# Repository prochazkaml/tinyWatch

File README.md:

# tinyWatch

A simple ATtiny3224-based wristwatch with an OLED display, a couple of buttons and a CR2032 battery.

To build your very own tinyWatch, you'll need to source the components, get a PCB made (or make it yourself, if you're brave enough), get the plastic parts 3D printed (or, again, print it yourself if you've already got a printer) and find a compatible 18 mm watch band + push pin (or edit the .scad files if you've got some other one).

## Plastic parts

The plastic parts of the tinyWatch are expected to be 3D printed (tested FDM, but SLA should work as well). They consist of:

- the back piece where the battery and PCB will be fit
- the front piece which will hold the OLED panel as well as the buttons in place, it also contains a pair of holes at each end for fitting a watch band push pin
- OLED support piece which will make the panel not fall inside of the watch
- 3x button caps

You can find these in the [hw/3D](https://github.com/prochazkaml/tinyWatch/tree/master/hw/3D) directory in .stl format with the .scad source files are available as well.

These parts are held together with an **M3 nut and M3x6 screw**.

## PCB & Hardware

The circuit diagram as well as the PCB were designed in KiCad, the project files are available in the [hw/kicad](https://github.com/prochazkaml/tinyWatch/tree/master/hw/kicad) directory. Many prototype PCB manufacturers support uploading raw KiCad files directly without the need to generate Gerber files. Recommended PCB thickness is 1.6 mm.

Of course, you will then need to populate the manufactured PCB with components. The bill of materials is available [here](https://github.com/prochazkaml/tinyWatch/blob/master/hw/kicad/tinywatch.csv) in CSV format. In summary, you'll need:

|Component|Package|Qty|DigiKey Part Number|
|-|-|-|-|
|4.7 μF capacitor|0603|1|1276-1044-1-ND|
|1 μF capacitor|0603|5|1276-1946-1-ND|
|2.2 μF capacitor|0603|1|1276-1040-1-ND|
|10 μF capacitor|0603|1|1276-1119-1-ND|
|1N4148W diode|SOD-123|1|311-4.70KHRTR-ND|
|4-pin straight female header|4x2.54 pitch|1|S7037-ND|
|SSD1306 128x64 0.96" OLED panel|30 pin flat ribbon, 0.7 mm pitch|1|3190-DLC0096DNOG-W-5-ND (but you can probably get it much cheaper [elsewhere](https://www.aliexpress.com/item/1005006114087000.html))|
|910k resistor|0603|1|13-AC0603FR-07910KLTR-ND|
|4.7k resistor|0603|1|311-4.70KHRTR-ND|
|Push button|6.7x4.1 mm|3|CKN12330-1-ND|
|ATtiny3224|SOIC-14|1|150-ATTINY3224-SSURCT-ND|
|32.768 kHz oscillator|3.2x2.5 mm|1|50-ECS-327TXO-30-CT-ND|

What is not included in the BOM is a **CR2032** battery, with specially shaped nickel strips welded to its terminals.
The assembly instructions below go into more detail on how to prepare and connect the battery correctly.

A cheap and perfectly usable watch band is available for example from [here](https://www.aliexpress.com/item/1005002369169370.html), just remember to select the 18 mm option. I personally opted for the "ML-Black" variant, it works just fine; it even comes with the required push pins embedded into the straps themselves.

## Assembly instructions

The hardware assembly instructions are available in [a separate document](ASSEMBLY.md).

Please note that the document already assumes that you have already assembled the required components onto the tinyWatch mainboard (excluding the battery).

## Firmware building instructions

The tinyWatch's firmware is written in Rust, so you'll need the Rust toolchain to be installed.

Bulding the firmware is as easy as running the following command:

```bash
cargo build --release
```

**NOTE**: This firmware is currently only compatible with revision 2 hardware with the new ATtiny3224 microcontroller. The old revision 1 hardware is only supported by the [old C-based firmware](https://github.com/prochazkaml/tinyWatch/tree/2073f80b21bf5213d320747aeb9541f89d2ae41b).

If you have a [serialupdi](https://github.com/SpenceKonde/AVR-Guidance/blob/master/UPDI/jtag2updi.md) programmer attached to the PC as well as the watch and want to upload the firmware to the watch, run the following:

```bash
avrdude -p attiny3224 -c serialupdi -P /dev/ttyUSB0 -v -U flash:w:target/avr-none/release/tinywatch.elf
```

## Power consumption

The watch consumes roughly **4.4 mA** while the screen is on, and about **3.4 μA** while the screen is off.

If you look at your watch for a total of 5 minutes each day, that would result in about **447 μAh** of power consumption **per day**. With this usage, the 220 mAh battery in the watch should last **more than a year**.

These measurements were taken using Nordic's [Power Profiler Kit 2](https://www.nordicsemi.com/Products/Development-hardware/Power-Profiler-Kit-2). The [raw capture file](doc/tinywatch_power_consumption.ppk2) can be viewed in the Power Profiler applet of the free and open source [nRF Connect for Desktop](https://www.nordicsemi.com/Products/Development-tools/nRF-Connect-for-Desktop) software.

## Setup

After flashing the firmware, you will want to set up the clock.
To do that, press the **left and right button** at simultaneously.
Then, using the **left** and **right** button, you will set the value on-screen and then press the **middle** button to confirm your selection and move onto the next value or finish the clock setup if you're done.
You will be asked at the end whether the entered values are correct.

## Oscillator calibration

> [!NOTE]  
> Revision 2 hardware uses a high quality temperature-compensated crystal oscillator with at most ±5 ppm of error, resulting in less than 0.5 seconds of drift per day.
> With this hardware, this option should be left alone.

If you experience severe drifts with the watch (more than 1 second per day), it is possible to trim the oscillator to a more precise value.

To remedy this issue, press the **left and middle button** together to enter the clock calibration menu.
There, you will be presented by a 16-bit hex value (the default is 8000, corresponding to the 32.768 kHz of the main oscillator).
With the **left** and **right** button, you can move the cursor.

To edit a value of a digit, press the **middle** button (the cursor will appear above the digit so that it is apparent what the buttons currently do)
and adjust the value using the **left** and **right** button.

To confirm your choice, press the **middle** button again to go back to cursor mode. Choose `Done` and press the **middle** button to exit.

## General usage

Once your watch is set up with the correct time, it is now ready to serve your everyday needs of checking the time.
Simply push any of its buttons and it will light up for a few seconds to tell you the time, before turning off again to conserve power.

---

That's it! Enjoy your watch. More features coming soon ;)

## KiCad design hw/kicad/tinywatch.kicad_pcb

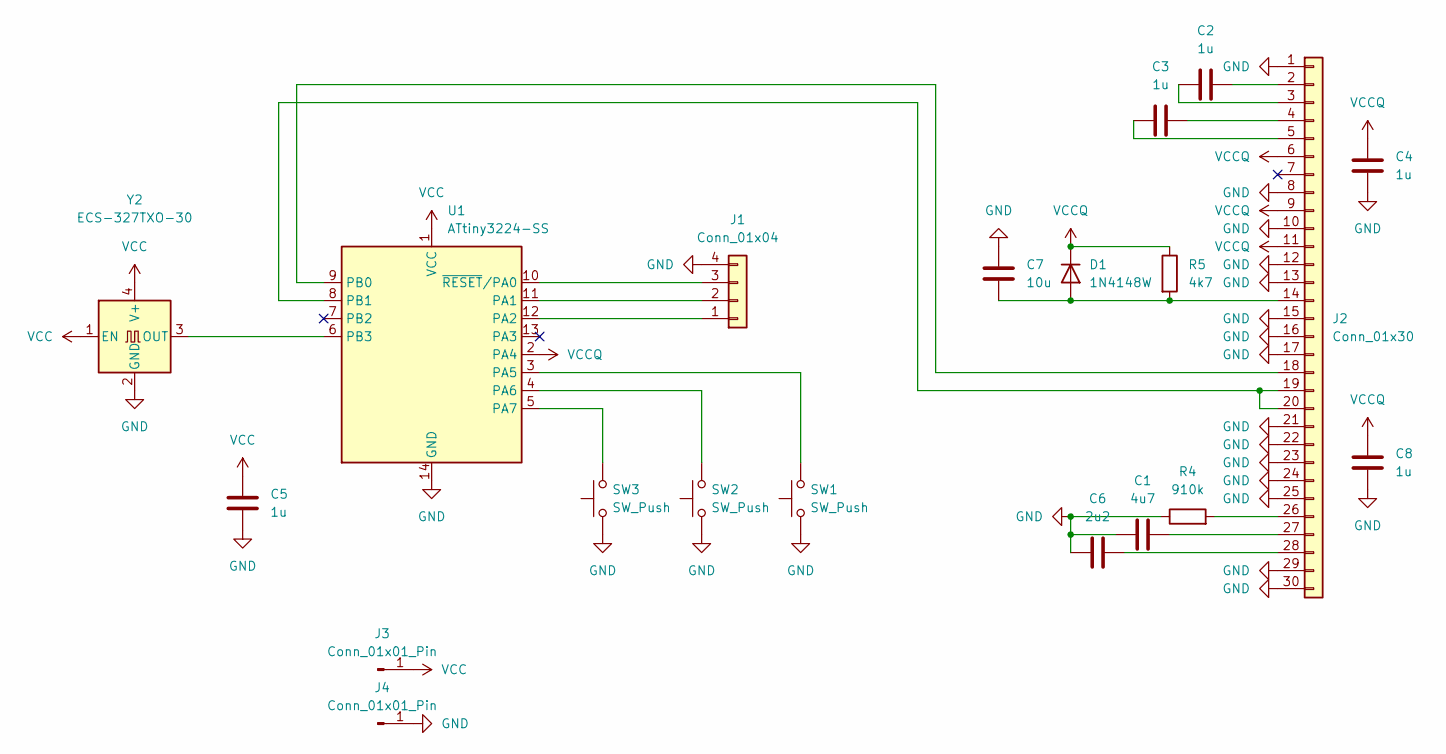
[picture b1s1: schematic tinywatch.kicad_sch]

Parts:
C1: 4u7; C_0603_1608Metric_Pad1.08x0.95mm_HandSolder
C2, C3, C4, C5, C8: 1u; C_0603_1608Metric_Pad1.08x0.95mm_HandSolder
C6: 2u2; C_0603_1608Metric_Pad1.08x0.95mm_HandSolder
C7: 10u; C_0603_1608Metric_Pad1.08x0.95mm_HandSolder
D1: 1N4148W; D_SOD-123
J1: Conn_01x04; PinSocket_1x04_P2.54mm_Horizontal
J2: Conn_01x30; OLED-128O064D
J3, J4: Conn_01x01_Pin; SolderWire-0.25sqmm_1x01_D0.65mm_OD1.7mm
R4: 910k; R_0603_1608Metric_Pad0.98x0.95mm_HandSolder
R5: 4k7; R_0603_1608Metric_Pad0.98x0.95mm_HandSolder
SW1, SW2, SW3: SW_Push; SW_DIP_SPSTx01_Slide_6.7x4.1mm_W6.73mm_P2.54mm_LowProfile_J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
U1: ATtiny3224-SS; SOIC-14_3.9x8.7mm_P1.27mm
Y2: ECS-327TXO-30; Oscillator_SMD_Abracon_ASE-4Pin_3.2x2.5mm

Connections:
GND: C1.1, C4.2, C5.2, C6.1, C7.1, C8.2, J1.4, J2.1, J2.8, J2.10, J2.12, J2.13, J2.15, J2.16, J2.17, J2.21, J2.22, J2.23, J2.24, J2.25, J2.29, J2.30, J4.1, R4.1, SW1.1, SW2.1, SW3.1, U1.14 (GND), Y2.2 (GND)
unnamed: C7.2, D1.2 (A), J2.14, R5.2
unnamed: J1.1, U1.12 (PA2)
unnamed: J1.2, U1.11 (PA1)
unnamed: J1.3, U1.10 (~RESET/PA0)
unnamed: C2.2, J2.2
unnamed: C2.1, J2.3
unnamed: C3.2, J2.4
unnamed: C3.1, J2.5
unnamed: J2.18, U1.9 (PB0)
unnamed: J2.19, J2.20, U1.8 (PB1)
unnamed: J2.26, R4.2
unnamed: C1.2, J2.27
unnamed: C6.2, J2.28
unnamed: SW1.2, U1.3 (PA5)
unnamed: SW2.2, U1.4 (PA6)
unnamed: SW3.2, U1.5 (PA7)
unnamed: U1.6 (PB3), Y2.3 (OUT)
VCC: C5.1, J3.1, U1.1 (VCC), Y2.1 (EN), Y2.4 (V+)
VCCQ: C4.1, C8.1, D1.1 (K), J2.6, J2.9, J2.11, R5.1, U1.2 (PA4)

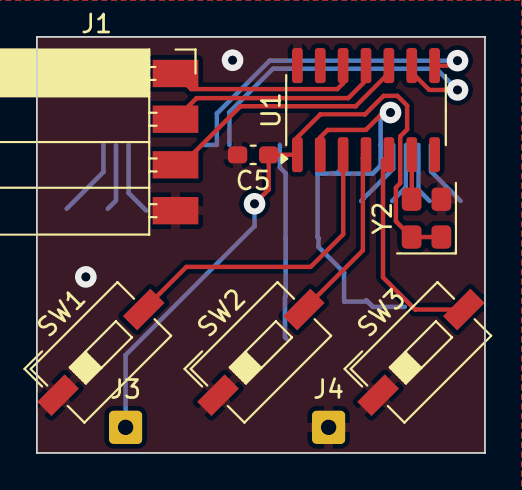
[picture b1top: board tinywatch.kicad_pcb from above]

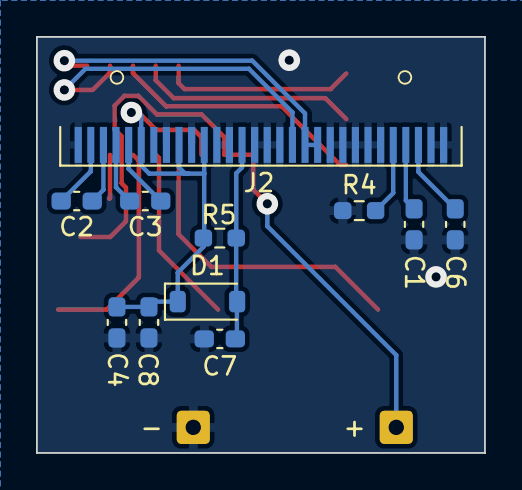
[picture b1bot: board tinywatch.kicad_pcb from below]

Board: 2 copper layers, 24.9 x 23.1 mm, 20 parts (11 on the bottom side), 20 nets.

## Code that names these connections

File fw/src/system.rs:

use avr_device::attiny3224::Peripherals;

pub fn peri() -> Peripherals {
	unsafe { core::mem::transmute(()) } // The Peripherals struct literally is 0 bytes in size anyways
}

pub fn delay(ms: usize) {
	for _ in 0..ms {
		avr_device::asm::delay_cycles(5000); // At 5 MHz
	}
}

pub fn low_power_delay(ms: usize) {
	for _ in 0..ms {
		avr_device::asm::delay_cycles(312); // At 312.5 kHz-ish
	}
}

#[inline]
pub fn access_protected_io() {
	peri().CPU.ccp().write(|reg| reg.ccp().ioreg());
}

/// Puts the CPU into high-performance mode (5 MHz).
pub fn enter_high_performance() {
	access_protected_io();
	peri().CLKCTRL.mclkctrlb().write(|reg| reg
		.pdiv()._4x()
		.pen().set_bit());
}

/// Puts the CPU into low-power mode (312.5 kHz).
pub fn enter_low_power() {
	access_protected_io();
	peri().CLKCTRL.mclkctrlb().write(|reg| reg
		.pdiv()._64x()
		.pen().set_bit());
}

/// Initializes the microcontroller.
pub fn init() {
	let peri = peri();

	// Set correct interrupt location

	access_protected_io();
	peri.CPUINT.ctrla().write(|reg| reg.ivsel().set_bit());

	// Set pullups on all pins, otherwise they will oscillate → consume power

	peri.PORTA.dir().write(|reg| reg
		.pa0().clear_bit()
		.pa1().clear_bit()
		.pa2().clear_bit()
		.pa3().clear_bit()
		.pa4().clear_bit()
		.pa5().clear_bit()
		.pa6().clear_bit()
		.pa7().clear_bit());

	peri.PORTB.dir().write(|reg| reg
		.pb0().clear_bit()
		.pb1().clear_bit()
		.pb2().clear_bit()
		.pb3().clear_bit());

	// TODO - is there a less retarded way to do all of this?
	// the assembly for the following looks about as you would expect

	peri.PORTA.pin0ctrl().write(|reg| reg.pullupen().set_bit());
	peri.PORTA.pin1ctrl().write(|reg| reg.pullupen().set_bit());
	peri.PORTA.pin2ctrl().write(|reg| reg.pullupen().set_bit());
	peri.PORTA.pin3ctrl().write(|reg| reg.pullupen().set_bit());
	peri.PORTA.pin4ctrl().write(|reg| reg.pullupen().set_bit());
	peri.PORTA.pin5ctrl().write(|reg| reg.pullupen().set_bit());
	peri.PORTA.pin6ctrl().write(|reg| reg.pullupen().set_bit());
	peri.PORTA.pin7ctrl().write(|reg| reg.pullupen().set_bit());

	peri.PORTB.pin0ctrl().write(|reg| reg.pullupen().set_bit());
	peri.PORTB.pin1ctrl().write(|reg| reg.pullupen().set_bit());
	peri.PORTB.pin2ctrl().write(|reg| reg.pullupen().set_bit());
	peri.PORTB.pin3ctrl().write(|reg| reg.pullupen().set_bit());
}

/// Enters sleep mode. Will wake up with the next interrupt.
pub fn sleep() {
	// Enable standby mode
	
	peri().SLPCTRL.ctrla().write(|reg| reg
		.smode().stdby()
		.sen().set_bit());

	avr_device::asm::sleep();
}

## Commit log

2022-04-29 Initial commit (already mostly works)
2022-04-29 Removed the pin change interrupt, just caused problems
2022-04-29 Shaved off over 100 bytes of code!
2022-04-29 Made the CPU clock control a bit more consistent
2022-04-29 Added a custom modified CRT to save space
2022-04-29 Got rid of updateleapyear()
2022-04-29 Squeezed out even more free space
2022-04-29 Even more savings have been achieved
2022-04-29 Moved the oscillator calibration vars to the user row
2022-04-29 Moved all string arrays + other goodies to the EEPROM
2022-04-29 Even more space savings (+ the fonts are sort of packed now)
2022-04-29 EVEN MORE SPACE SAVINGS!
2022-04-29 Reorganization + cleanup
2022-04-29 A bit more reorganization + more savings!
2022-04-30 VSCode was complaining 🤷
2022-04-30 More space savings + turbo 🚄
2022-05-24 Fixed some unreliability issues with the OLED
2022-06-25 When a submenu is invoked, wait for both buttons to be released
2022-06-25 Improved font "packing"
2022-06-25 Now using quicker-to-access VPORT registers
2022-06-26 Not providing debug info in main.elf, useless anyway
2022-06-26 Overall space optimization + removed leap year support (unnecessary)
2022-06-26 Made the build script easier to use (no need to pass any params anymore)
2022-06-26 min_sprintf destination is now hard-coded
2022-06-26 Forced the framebuffer to be exactly at addr 0x3800
2022-06-26 Added a program for testing the rendering of the large font
2022-06-27 Even more flash space savings (thanks in part to inline assembly)
2022-06-27 Improved font compression
2022-06-27 More slight flash space savings
2022-06-28 Fixed docs
2022-06-28 Whoops
2022-06-30 Added the source code behind crtattiny1614.o
2022-06-30 Even more flash space savings
2022-06-30 Added compilation instructions for gcrt1.S
2022-06-30 Added info for dumping symbols
2022-09-30 Goodbye C, welcome AVR ASM!
2022-09-30 Create LICENSE
2022-09-30 Renamed .inc def file to .asm
2022-09-30 Added printable 3D models + scad source files
2022-09-30 Added KiCad source files
2022-09-30 Added BOM
2024-11-09 Turns out I really do not like assembly
2024-11-09 The watch will no longer drain the battery when you accidentally put a heavy box on top of the buttons and leave it like that overnight
2024-11-09 Updated docs
2024-11-09 Removed dependance on the EEPROM
2024-11-09 Fixed typo
2024-11-09 R2 hardware
2024-11-09 Added FW support for R2 HW
2024-11-09 Updated BOM
2024-11-09 Updated BOM and README
2025-07-20 Left a trace disconnected, whoops
2025-07-20 Replaced the crystal with a more precise TXCO
2025-07-20 Replaced TXCO footprint with a more solderable variant
2025-08-02 Made the buttons easier to fit
2025-08-02 Rust rewrite was imminent
2025-08-02 Added labels for "+" and "-"
2025-08-02 Added the "elsewhere"
2025-08-02 `--release` produces slightly smaller binaries
2025-08-02 Removed Makefile
2025-08-03 Reduced power consumption by selecting the external clock instead of crystal
2025-08-03 Tíme setup now has "cancel" instead of "retry"
2025-08-03 Added assembly instructions
2025-08-03 Modified OLED support to better suit the current hardware revision
2025-08-03 Added power consumption blerb
2025-08-15 Added an example watch band
2025-08-17 Holding down the button no longer causes excessive CPU load
2025-08-17 -90 bytes by removing Peripherals::steal()
2025-08-17 Rtc methods are no longer &self
2025-08-17 -570 bytes by making the OLED framebuffer global
2025-08-17 Revert "Rtc methods are no longer &self"
    This reverts commit 002ed1289d6f17a94cd965113bc884d489dd25ae.
2025-08-30 Updated to ATtiny3224
2025-08-30 Updated Cargo config for ATtiny3224
2025-08-31 Updated Rust nightly version to support the ATtiny3224
